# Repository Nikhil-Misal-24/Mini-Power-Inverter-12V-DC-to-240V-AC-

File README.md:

# ⚡ Mini Power Inverter

### `12V DC → 240V AC`

<p align="center">
  <b>A compact switching-based DC–AC power inverter developed as a practical power-electronics and PCB design project.</b>
</p>

---

## 🚀 Project at a Glance

> **A compact 12V DC → 240V AC inverter built around an IR2153 switching/driver stage, IRLZ24 MOSFET power switches, and a transformer-based voltage conversion stage.**

The project focuses on turning a theoretical inverter topology into a **real, compact hardware implementation**, covering the complete development cycle from circuit design to PCB fabrication, assembly, soldering, testing, and troubleshooting.

### 🔋 Input

**12V DC**

### ⚡ Conversion

**High-frequency switching + transformer**

### 🔌 Output

**240V AC nominal**

### 🧩 Controller

**IR2153**

### 🔧 Power Switch

**IRLZ24 MOSFET**

### 📐 PCB

**~65 × 35 mm**

---

# 🧠 How It Works

```text
                 ┌──────────────────┐
                 │   12V DC INPUT   │
                 └────────┬─────────┘
                          │
                          ▼
                 ┌──────────────────┐
                 │     IR2153       │
                 │ Oscillator /     │
                 │ Gate Driver      │
                 └────────┬─────────┘
                          │
                          ▼
                 ┌──────────────────┐
                 │   IRLZ24         │
                 │ MOSFET Switching │
                 └────────┬─────────┘
                          │
                          ▼
                 ┌──────────────────┐
                 │   TRANSFORMER    │
                 │   Step-Up Stage  │
                 └────────┬─────────┘
                          │
                          ▼
                 ┌──────────────────┐
                 │   240V AC OUT    │
                 └──────────────────┘
```

### 🔄 Conversion Process

**01 — DC Input**

A 12V DC source supplies energy to the inverter.

**02 — Oscillation**

The IR2153 generates the switching signal required to control the power MOSFET stage.

**03 — Power Switching**

IRLZ24 MOSFETs rapidly switch the DC supply through the transformer primary.

**04 — Voltage Transformation**

The transformer steps up the switched waveform to a high-voltage AC output.

**05 — AC Output**

The secondary side provides a nominal 240V AC output under the designed operating conditions.

---

# ⚙️ Technical Specifications

| Parameter      | Value                          |
| -------------- | ------------------------------ |
| 🔋 Input       | **12V DC**                     |
| ⚡ Output       | **240V AC nominal**            |
| 🔄 Conversion  | **DC → AC**                    |
| 🎛️ Driver     | **IR2153**                     |
| 🔧 MOSFET      | **IRLZ24**                     |
| 🧲 Transformer | **Step-Up Transformer**        |
| 📐 PCB Size    | **~65 × 35 mm**                |
| 🛠️ PCB        | **Custom Designed**            |
| 🎯 Application | **Educational / Experimental** |

> Actual output voltage, waveform, efficiency and power capability depend on the transformer, component values, input supply, switching configuration and load.

---

# 🧩 Hardware Architecture

### Control & Switching Stage

The **IR2153** forms the oscillator/driver section responsible for generating the switching signals.

### Power Stage

The **IRLZ24 MOSFETs** handle the high-current switching required to transfer energy from the 12V DC source into the transformer.

### Voltage Conversion Stage

The transformer performs the required voltage step-up from the low-voltage switching stage to the high-voltage AC output.

---

# 🛠️ Design Journey

```text
Concept
   ↓
Circuit Design
   ↓
Component Selection
   ↓
Schematic Development
   ↓
PCB Layout
   ↓
PCB Fabrication
   ↓
Component Assembly
   ↓
Soldering
   ↓
Testing
   ↓
Debugging
   ↓
Final Hardware
```

This project was developed with a focus on **practical hardware implementation**, not just simulation.

---

# 🖥️ PCB Design

The inverter was implemented on a compact custom PCB.

### PCB Design Goals

* Compact footprint
* Practical component placement
* Reduced high-current path length
* Organized power-stage routing
* Easy component identification
* Reliable soldering and assembly
* Hardware-oriented layout

**Approximate PCB Dimensions**

```text
65 mm × 35 mm × 19 mm
```

---

# 📸 Project Gallery

> Replace the paths below with your actual repository images.

### 🔧 Final PCB

### 🖥️ PCB Layout

### 📐 Schematic

---

# 🔬 Engineering Focus

This project explores several important electronics concepts:

| Area                | Implementation           |
| ------------------- | ------------------------ |
| Power Electronics   | DC–AC conversion         |
| Switching           | MOSFET-based switching   |
| Gate Driving        | IR2153                   |
| Power Semiconductor | IRLZ24                   |
| Magnetic Components | Transformer              |
| PCB Engineering     | Custom PCB               |
| Hardware            | Through-hole components  |
| Testing             | Hardware debugging       |
| Manufacturing       | PCB assembly & soldering |

---

# 💡 What I Learned

Through this project, I gained practical experience with:

* Switching inverter architectures
* MOSFET power switching
* Gate-driver circuits
* Transformer-based voltage conversion
* Power PCB layout
* High-current PCB routing
* Component selection
* Hardware assembly
* Soldering
* Circuit debugging
* Practical testing
* Power-electronics safety considerations

---

# 🔮 Future Development

The next version could include:

* [ ] Output voltage feedback
* [ ] Closed-loop voltage regulation
* [ ] Over-current protection
* [ ] Short-circuit protection
* [ ] Thermal protection
* [ ] Battery low-voltage cutoff
* [ ] Output voltage monitoring
* [ ] Frequency monitoring
* [ ] Improved waveform quality
* [ ] Higher conversion efficiency
* [ ] Better thermal management
* [ ] Protective enclosure

---

# 📊 Project Status

<p align="center">

| Development Stage   | Status                  |
| ------------------- | ----------------------- |
| Circuit Concept     | ✅ Completed             |
| Component Selection | ✅ Completed             |
| Schematic           | ✅ Completed             |
| PCB Design          | ✅ Completed             |
| PCB Fabrication     | ✅ Completed             |
| Assembly            | ✅ Completed             |
| Hardware Testing    | 🔧 In Progress / Update |
| Optimization        | 🚀 Future               |

</p>

---

# ⚠️ HIGH-VOLTAGE SAFETY

<div align="center">

### ⚠️ WARNING — 240V AC IS DANGEROUS

</div>

This project produces potentially **lethal high voltage**.

Do not touch exposed output terminals or conductors while the inverter is powered.

Always:

* Use proper insulation.
* Maintain adequate PCB clearance and creepage.
* Disconnect the DC supply before making modifications.
* Use appropriate measurement equipment.
* Avoid working alone around high voltage.
* Enclose the final hardware appropriately.

**This project is intended for educational and experimental purposes.**

---

# 📁 Repository Structure

```text
Mini-Power-Inverter-12V-DC-to-240V-AC/
│
├── 📁 Images/
│   ├── final-pcb.jpg
│   ├── pcb-layout.png
│   └── schematic.png
│
├── 📁 PCB/
│   ├── schematic/
│   └── layout/
│
├── 📁 Documentation/
│
├── 📄 README.md
└── 📄 LICENSE
```

---

# 🎯 Project Objectives

### Primary Objective

Develop a compact practical inverter capable of converting a **12V DC source into a nominal 240V AC output** using a switching-based power stage.

### Secondary Objectives

* Understand inverter topology.
* Gain practical MOSFET switching experience.
* Design a compact PCB.
* Understand transformer-based voltage conversion.
* Develop hardware debugging skills.
* Build practical power-electronics experience.

---

# 👨‍💻 Developer

## Nikhil Misal

**Electronics & Communication Engineering Student**

**Focus Areas**

`Embedded Systems` · `PCB Design` · `Electronics Hardware` · `Power Electronics` · `IoT` · `Microcontrollers`

---

# 🌟 Why This Project?

This project represents a complete **hardware development workflow**:

```text
Idea
 ↓
Engineering
 ↓
Design
 ↓
PCB
 ↓
Assembly
 ↓
Testing
 ↓
Optimization
```

Rather than treating electronics as only theoretical concepts, this project focuses on **building, testing, debugging, and improving real hardware.**

---

<p align="center">

### ⚡ Built with Electronics • Designed with Purpose • Tested in Hardware

</p>

<p align="center">

<b>⭐ If you find this project useful, consider starring the repository.</b>

</p>

---

## 📜 License

This repository is intended for educational and experimental use.

Refer to the repository's `LICENSE` file for the applicable licensing terms.

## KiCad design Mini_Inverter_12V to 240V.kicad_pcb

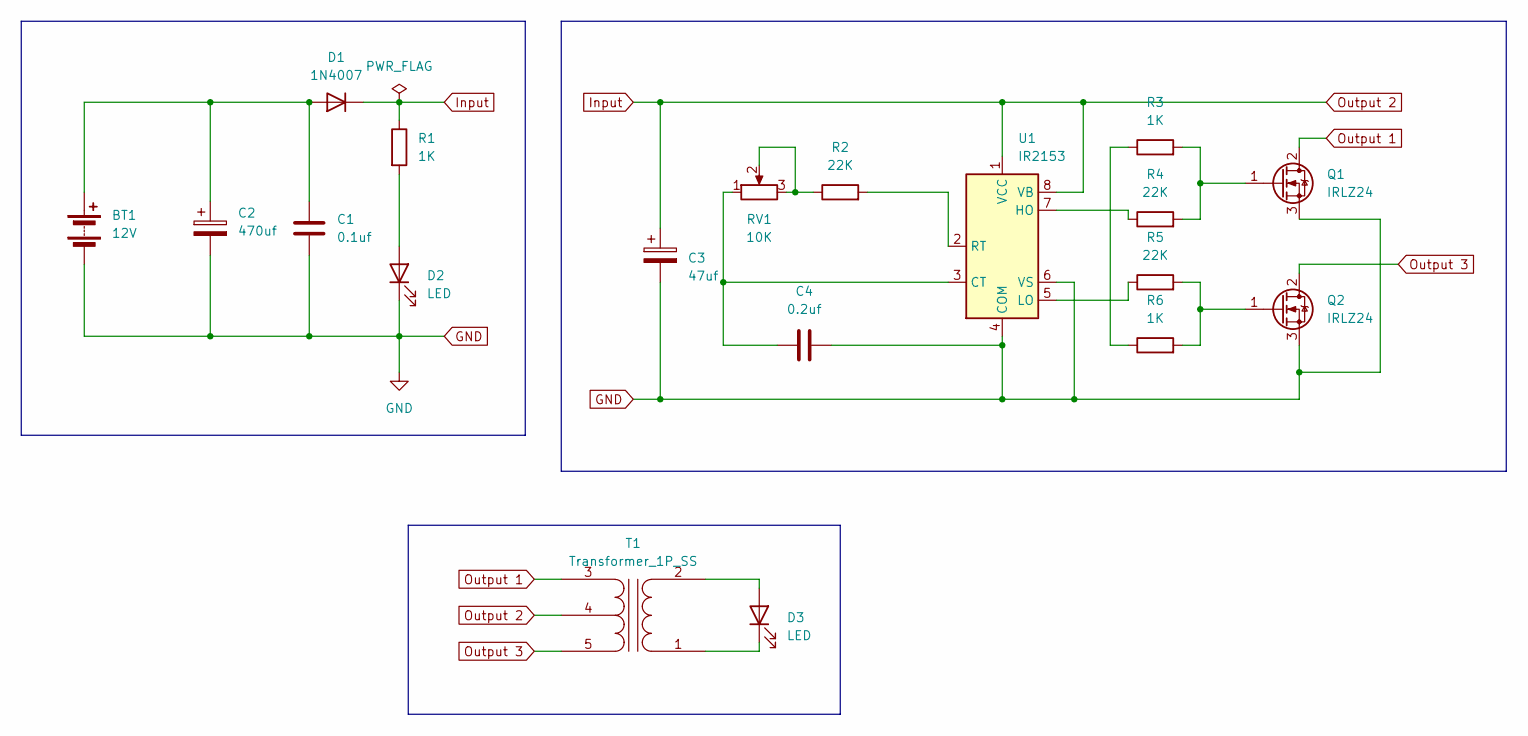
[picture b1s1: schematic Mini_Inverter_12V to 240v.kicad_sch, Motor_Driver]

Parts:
BT1: 12V; TerminalBlock_Xinya_XY308-2.54-2P_1x02_P2.54mm_Horizontal
C1: 0.1uf; CP_Radial_D6.3mm_P2.50mm
C2: 470uf; C_Disc_D3.0mm_W1.6mm_P2.50mm
C3: 47uf; CP_Radial_D5.0mm_P2.50mm
C4: 0.2uf; C_Disc_D3.0mm_W1.6mm_P2.50mm
D1: 1N4007; D_DO-41_SOD81_P10.16mm_Horizontal
D2: LED; LED_D5.0mm
D3: LED; TerminalBlock_Xinya_XY308-2.54-2P_1x02_P2.54mm_Horizontal
Q1, Q2: IRLZ24; TO-220-3_Vertical
R1, R3, R6: 1K; R_Axial_DIN0204_L3.6mm_D1.6mm_P5.08mm_Horizontal
R2, R4, R5: 22K; R_Axial_DIN0204_L3.6mm_D1.6mm_P5.08mm_Horizontal
RV1: 10K; Potentiometer_ACP_CA6-H2,5_Horizontal
T1: Transformer_1P_SS; TerminalBlock_Xinya_XY308-2.54-5P_1x05_P2.54mm_Horizontal
U1: IR2153; CERDIP-8_W7.62mm_SideBrazed

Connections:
GND: BT1.2 (-), C1.2, C2.2, C3.2, C4.2, D2.1 (K), Q1.3 (S), Q2.3 (S), U1.4 (COM), U1.6 (VS)
Input: C3.1, D1.1 (K), R1.1, T1.4 (SC), U1.1 (VCC), U1.8 (VB)
unnamed: BT1.1 (+), C1.1, C2.1, D1.2 (A)
unnamed: D2.2 (A), R1.2
unnamed: D3.2 (A), T1.2 (AB)
unnamed: D3.1 (K), T1.1 (AA)
unnamed: Q1.1 (G), R3.2, R4.2
unnamed: Q2.1 (G), R5.2, R6.2
unnamed: R2.1, RV1.2, RV1.3
unnamed: R3.1, R6.1
unnamed: C4.1, RV1.1, U1.3 (CT)
unnamed: R4.1, U1.7 (HO)
unnamed: R5.1, U1.5 (LO)
unnamed: R2.2, U1.2 (RT)
Output 1: Q1.2 (D), T1.3 (SA)
Output 3: Q2.2 (D), T1.5 (SB)

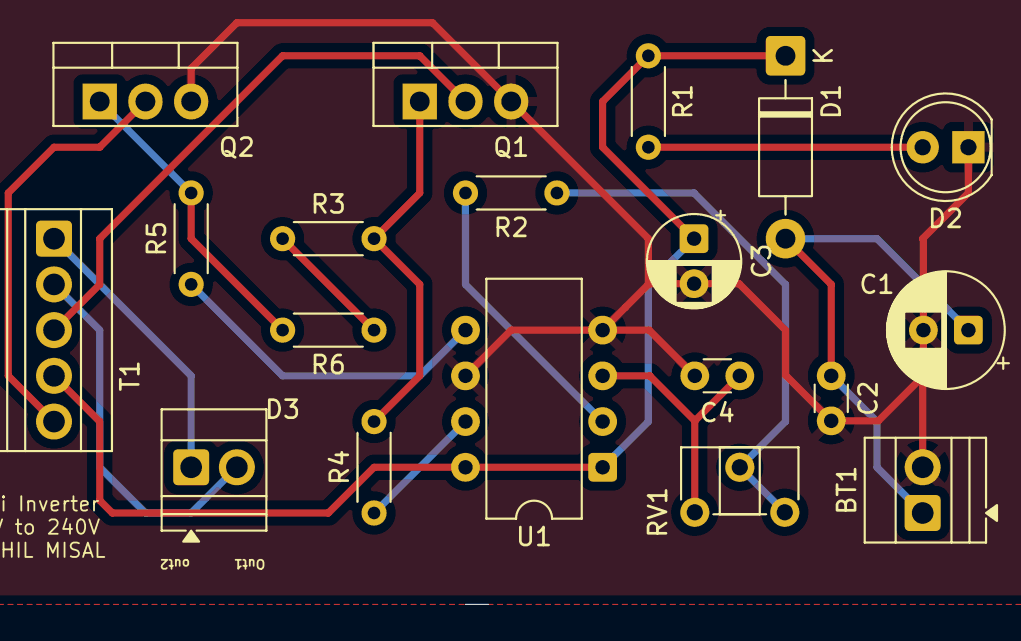
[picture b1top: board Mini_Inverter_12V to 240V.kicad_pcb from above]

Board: 2 copper layers, 19 parts (0 on the bottom side), 16 nets.

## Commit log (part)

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2026-03-02 Second Commit
2026-03-02 Add README for Mini Inverter project
    Added project overview, features, tools, working principle, and applications for the Mini Inverter.
